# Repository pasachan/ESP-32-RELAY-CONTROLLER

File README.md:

# ESP32 Relay Controller

**An 8-channel relay controller with Wi-Fi, an RS-485 field bus, and a 12 V power rail for downstream nodes.**
Designed as the master board for a small home-automation network: this board switches loads directly, talks to
the outside world over Wi-Fi, and powers and polls a chain of low-cost slave boards (ATtiny / STM32 class) over RS-485.

Open hardware. KiCad 10 source, fabrication outputs, BOMs with LCSC part numbers, and a pick-and-place file are all in this repository. Rev 1 has been manufactured.

---

## Features

- **ESP32-WROOM-32D** (16 MB flash) — Wi-Fi + Bluetooth, USB-C programming via CH340C with auto-reset
- **8 × SPDT relays** (SRD-05VDC, 10 A contacts), driven by a ULN2803A with built-in flyback clamps, each brought out to a 3-way screw terminal (NO / COM / NC)
- **RS-485 half-duplex master** — MAX3485 (3.3 V), SM712 surge protection, jumper-selectable 120 Ω termination, fail-safe biasing
- **12 V field bus power** on the RS-485 connector, so slave nodes need no local supply
- **12 V input** with P-FET reverse-polarity protection, bidirectional TVS, and an LC input filter
- Two synchronous bucks (LMR51430): 5 V for relay coils, 3.3 V for logic — the 3.3 V rail also runs from USB alone for bench programming
- One dry-contact input (pull-up, RC filter, ESD clamp), active buzzer, WS2812B status LED, rail indicator LEDs
- RESET / BOOT / user (WPS) buttons, 2 mm mounting holes, 124.75 × 68 mm, 2-layer

---

## Block diagram

```mermaid
flowchart LR
    J1["12 V input"] --> Q1["IRF4905<br/>reverse-polarity FET"] --> L3["LC input filter"] --> V12["+12 V rail"]
    D2["SMBJ18CA TVS"] -.clamps.-> J1
    V12 --> U2["LMR51430<br/>buck → 5 V"] --> V5["+5 V coil rail"]
    V12 --> D3["Schottky OR"] --> U3["LMR51430<br/>buck → 3.3 V"] --> V33["+3.3 V logic"]
    USB["USB-C"] --> U4["USBLC6 ESD"] --> U6["CH340C"] <-->|"UART0 + auto-reset"| U1
    USB -->|"VBUS"| D4["Schottky OR"] --> U3
    V33 --> U1["ESP32-WROOM-32D"]
    U1 -->|"8 × GPIO"| U7["ULN2803A"] -->|"8 × coil"| K["K2 … K9<br/>SRD-05VDC SPDT"] --> JT["8 × NO/COM/NC<br/>screw terminals"]
    V5 --> K
    U1 <-->|"UART2 + DE/RE"| U9["MAX3485<br/>RS-485"] --> D6["SM712 TVS"] --> J12["Field bus<br/>12V · A · B · GND"]
    V12 --> J12
    U1 --> BZ["Buzzer"]
    U1 --> LED["WS2812B"]
    IN["Dry-contact input"] --> U1
```

---

## Specifications

| | |
|---|---|
| Supply | 12 V DC nominal (LMR51430 bucks accept 4–36 V; TVS clamps at 18 V standoff) |
| Board draw @ 12 V | ~170 mA idle · ~520 mA worst case (all relays + Wi-Fi TX) |
| Field-bus power budget | ~1.8 A at 12 V on J12 — set by the 1.0 mm feed trace (2.4 A @ 10 °C rise) less the board's own draw; L3 is rated 4.5 A |
| Relay contacts | SPDT, 10 A / 250 VAC rated · **PCB traces sized for ≤ 2.3 A at 12–30 V** (see [design notes](docs/design-notes.md#relay-bank-and-switched-load-clearances)) |
| Relay coil drive | ~4.0 V at the coil vs 3.75 V pick-up spec — all eight channels |
| RS-485 | Half-duplex, 3.3 V transceiver, 120 Ω termination via JP1, 330 Ω fail-safe bias (this node only) |
| USB | USB 2.0 Full Speed (CH340C), USB-C receptacle, 5.1 k CC pull-downs, VBUS ESD array |
| Logic level | 3.3 V throughout; WS2812B fed through a series diode so 3.3 V data meets its V<sub>IH</sub> |
| Dimensions | 124.75 × 68 mm, 1.6 mm FR-4, 2 layers, 1 oz copper |
| Mounting | 4 × Ø2.0 mm holes at the corners |

---

## Repository layout

```
esp32-relay-controller/
├── README.md
├── hardware/
│   ├── kicad/                     KiCad 10 project (schematic, PCB, custom rules, project symbol lib)
│   ├── fabrication/
│   │   ├── gerbers/               RS-274X gerbers + Excellon drill files (fab layers only)
│   │   ├── esp32-relay-controller-gerbers.zip
│   │   ├── BOM.csv                Master BOM — every fitted part, SMD and through-hole, with LCSC + MPN
│   │   ├── BOM-JLCPCB.csv         SMD-only, JLCPCB column format
│   │   ├── BOM-PCBWay.csv         SMD-only, MPN-first for PCBWay
│   │   ├── CPL.csv                SMD pick-and-place (Designator / Mid X / Mid Y / Layer / Rotation)
│   │   └── README.md              How to order
│   └── images/                    Renders and layer plots
├── docs/
│   ├── schematic.pdf
│   ├── design-notes.md            Design decisions, the review process, and what changed as a result
│   └── pinout.md                  ESP32 GPIO map, relay ↔ terminal ↔ GPIO table, connector pinouts
└── firmware/
    ├── README.md                  Pin definitions and the gotchas that bite firmware authors
    └── self-test/                 Bring-up sketch — exercises every component, no libraries needed
```

---

## Getting boards made

Everything a fab needs is in [`hardware/fabrication/`](hardware/fabrication/). The short version:

1. Upload `esp32-relay-controller-gerbers.zip` for the bare PCB — 2 layer, 1.6 mm, 1 oz, any colour.
2. For SMD assembly, upload `BOM-JLCPCB.csv` + `CPL.csv` (JLCPCB) or `BOM-PCBWay.csv` + `CPL.csv` (PCBWay). 72 SMD parts, 35 lines.
3. Hand-fit the 25 through-hole parts: 8 relays, 11 screw-terminal blocks, the TO-220 FET, buzzer, three tact switches and the termination header. All are common parts; LCSC numbers are in `BOM.csv`.

See [`hardware/fabrication/README.md`](hardware/fabrication/README.md) for gerber-origin caveats, the one DFM query a fab may raise, and which parts are safe to substitute.

---

## Firmware quick reference

[`firmware/self-test/`](firmware/self-test/) is a bring-up sketch that exercises every fitted component and prints a pass/fail report over USB serial. Run it first on a new board. Full map in [`docs/pinout.md`](docs/pinout.md), gotchas in [`firmware/README.md`](firmware/README.md).

| Function | GPIO | Notes |
|---|---|---|
| Relay 1 … 8 (silkscreen order) | 14, 19, 25, 13, 23, 33, 32, 18 | Active-high into ULN2803A |
| RS-485 TX / RX / DE+RE | 17 / 16 / 2 | GPIO2 has a 10 k pull-down → receive mode at boot |
| Dry-contact input | 34 | Input-only pin, external 10 k pull-up, closes to GND |
| User button (WPS) | 35 | Input-only, 10 k pull-down, pressed = high |
| Buzzer | 26 | Via NPN, active-high |
| WS2812B data | 27 | Through 330 Ω |
| UART0 (USB) | 1 / 3 | CH340C with DTR/RTS auto-reset |
| I²C | 21 / 22 | Routed to pads but **no pull-ups fitted** in rev 1 |

---

## Design notes

The interesting engineering is in [`docs/design-notes.md`](docs/design-notes.md). Highlights:

- **Why the field bus carries 12 V and not 3.3 V** — cable drop and the thermal ceiling of a SOT-23-6 buck make 3.3 V distribution a dead end past a couple of nodes; regulating at each slave costs one LDO and removes the constraint.
- **Reverse-polarity protection with a P-FET, and why the TVS sits in front of it** — a unidirectional clamp ahead of the FET would short a reversed supply, so it's a bidirectional part.
- **Relay coil drive margin** — the SRD-05VDC needs 3.75 V to pull in; behind a ULN2803A the coil sees ~4.0 V. A series diode in the original design put one channel *under* the limit and was removed.
- **Driving a 5 V WS2812B from a 3.3 V GPIO** — a diode in the LED's supply drops V<sub>DD</sub> into the window where 3.3 V is a valid high, without a level shifter.
- **A KiCad DRC gotcha** — custom rules that match on auto-generated net names like `Net-(J2-Pin_1)` silently never fire. The rules in this project match on a netclass instead.
- **What the design review caught** — the board went through a full netlist, DRC, ERC and geometric-connectivity audit before ordering; the findings and fixes are documented.

---

## Status

| Revision | Date | Notes |
|---|---|---|
| **Rev 1** | Sep 2026 | Ordered. 0 DRC errors, 0 unconnected nets, all nets verified single-island. |
| **Rev 1** | Oct 2026 | **Built and brought up.** All eight relays, the buzzer, the WS2812B, both inputs, the RS-485 receiver and the USB programming path work. One firmware-level finding: the MAX3485's RO pin is tri-stated during transmit and has no pull-up, so it needs one enabled in software — [details](firmware/self-test/README.md#finding-ro-floats-during-transmit). |

Known rev 1 limitations and the planned rev 2 changes are listed at the end of the [design notes](docs/design-notes.md#rev-2-backlog).

---

## Licence

Copyright © 2026 Pareekshit Sachan.

This source describes Open Hardware and is licensed under the **CERN-OHL-P v2** (`SPDX-License-Identifier: CERN-OHL-P-2.0`). You may redistribute and modify this documentation and make products using it under the terms of the CERN-OHL-P v2 — see [`LICENSE`](LICENSE) or <https://cern.ch/cern-ohl>.

This documentation is distributed WITHOUT ANY EXPRESS OR IMPLIED WARRANTY, INCLUDING OF MERCHANTABILITY, SATISFACTORY QUALITY AND FITNESS FOR A PARTICULAR PURPOSE. Please see the CERN-OHL-P v2 for applicable conditions.

Symbols, footprints and 3D models from the KiCad libraries are used under the [KiCad library licence](https://www.kicad.org/libraries/license/) (CC-BY-SA 4.0 with exception). Datasheets referenced in the design notes remain the property of their manufacturers.

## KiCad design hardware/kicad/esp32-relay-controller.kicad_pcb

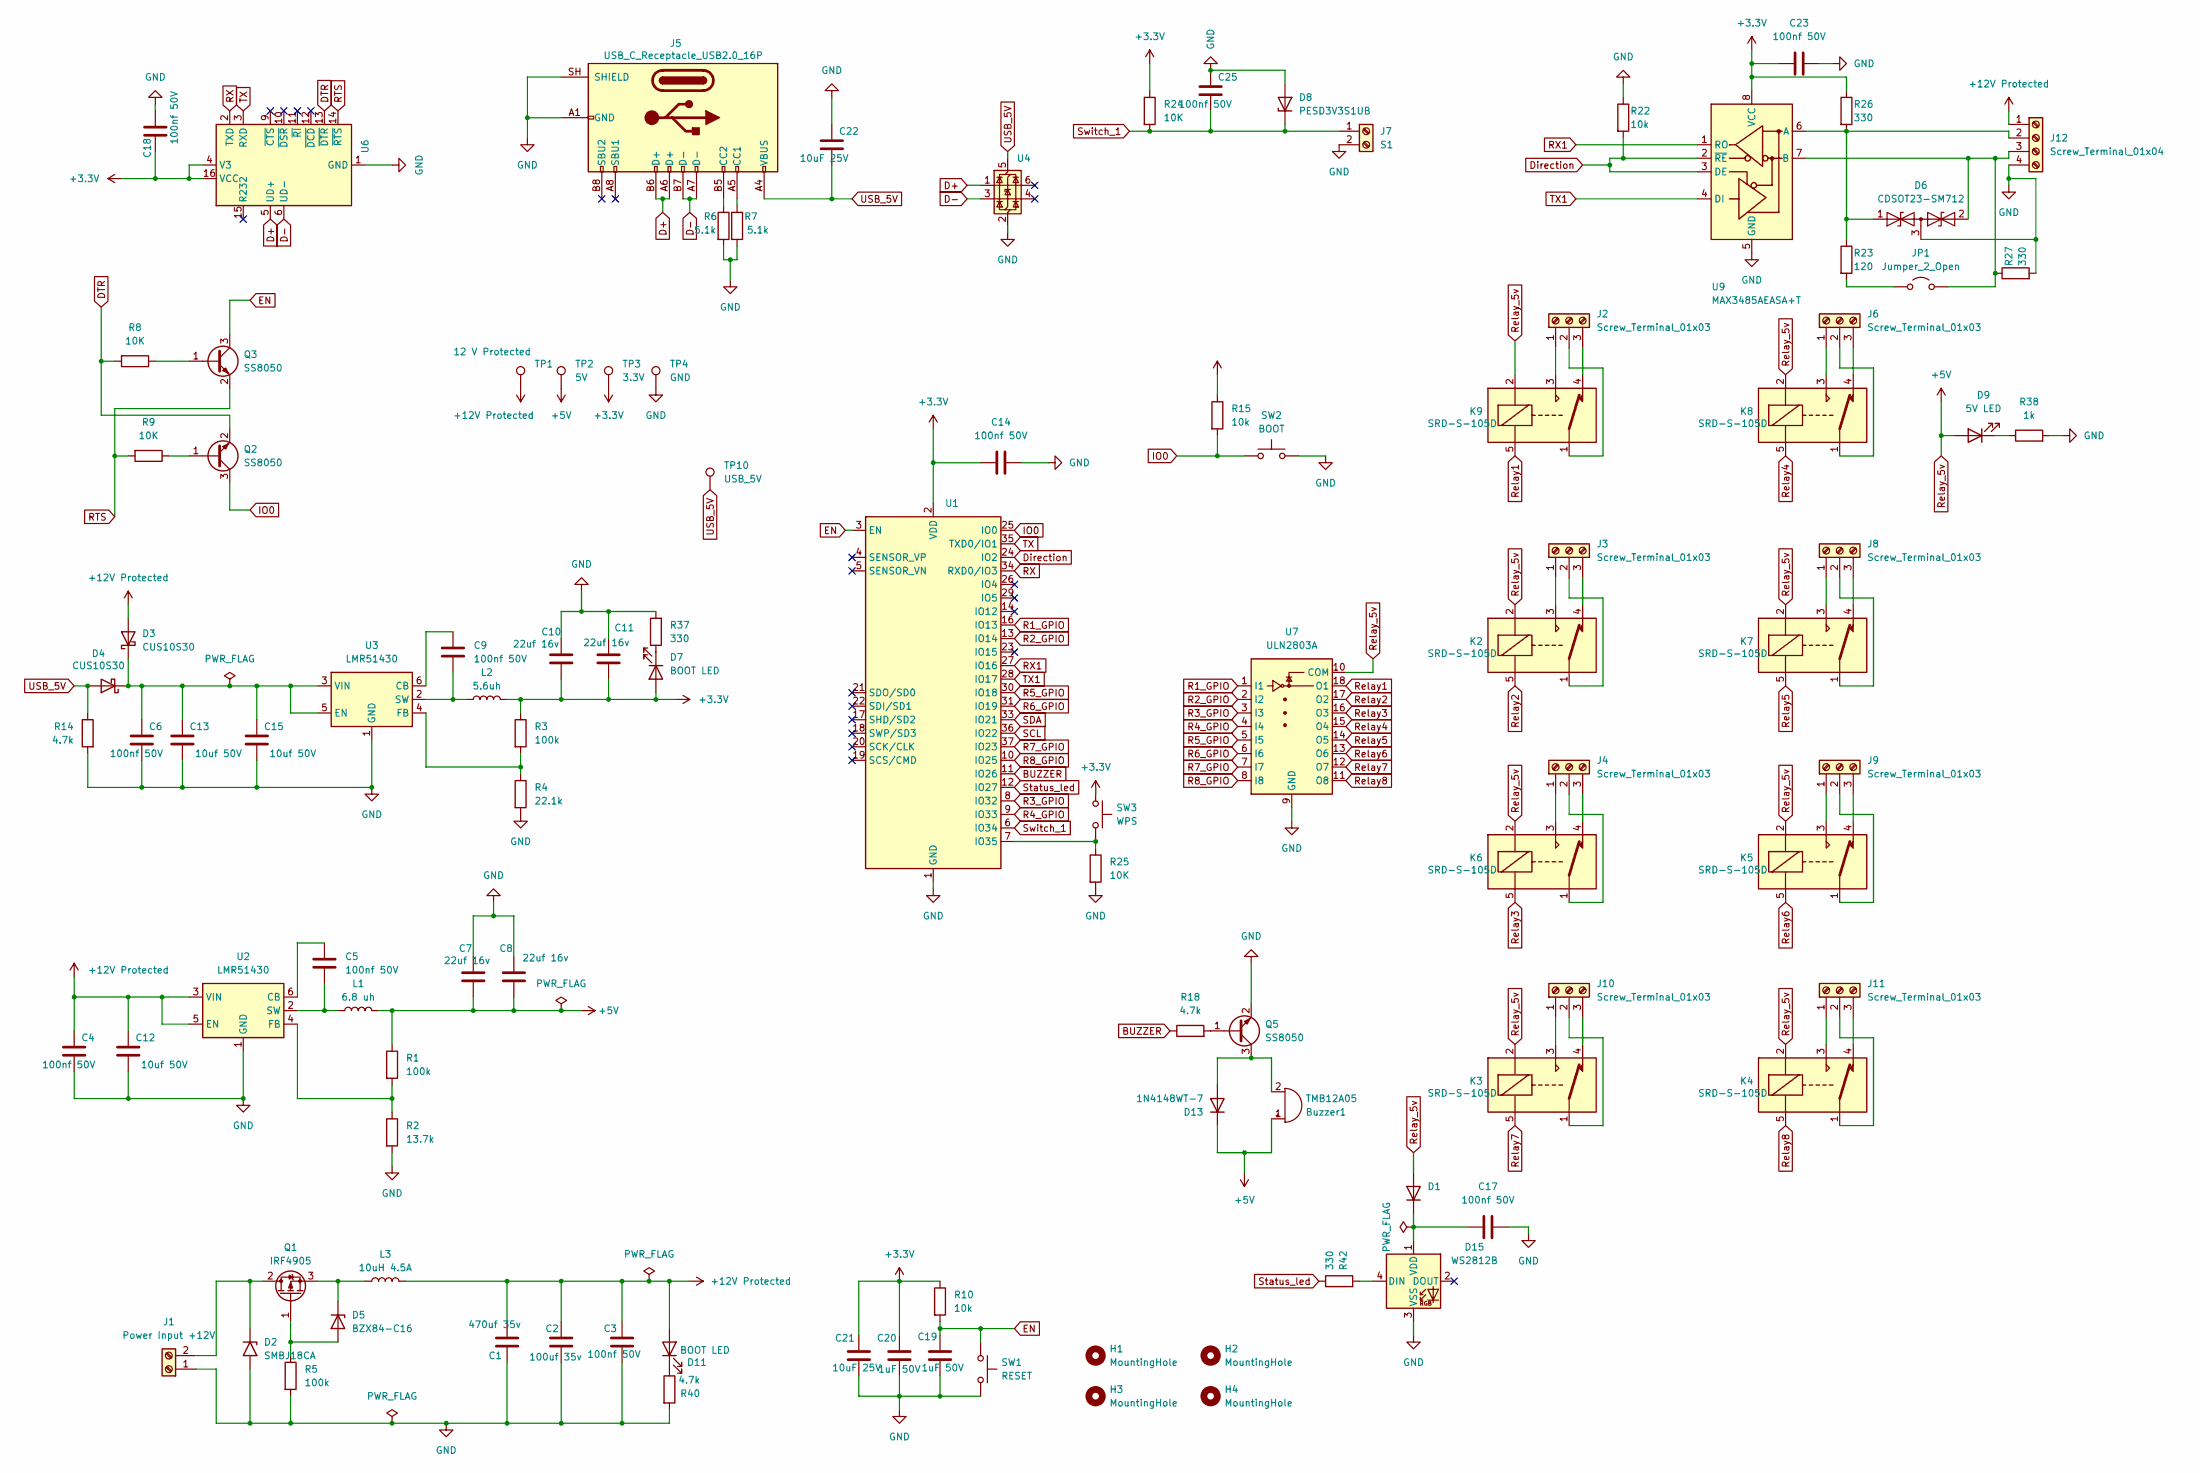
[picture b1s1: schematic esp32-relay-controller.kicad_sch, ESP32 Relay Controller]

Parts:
Buzzer1: TMB12A05; Buzzer_12x9.5RM7.6; MPN TMB12A05; LCSC C96093
C1: 470uf 35v; CP_Elec_10x10.5; MPN RVT1V471M1010 470UF 35V; LCSC C976030
C2: 100uf 35v; CP_Elec_6.3x7.7; MPN JBLM2101M035C070RTM 100UF 35V; LCSC C19270708
C3, C4, C5, C6, C9, C14, C17, C18, C23, C25: 100nf 50V; C_0603_1608Metric; MPN CL10B104KB8NNNC; LCSC C1591
C7, C8, C10, C11: 22uf 16v; C_0805_2012Metric; MPN CL21A226KOQNNNE; LCSC C296720
C12, C13, C15: 10uf 50V; C_0805_2012Metric; MPN GRM21BR61H106KE43L; LCSC C440198
C19, C20: 1uF 50V; C_0603_1608Metric; MPN CL10A105KB8NNNC; LCSC C15849
C21, C22: 10uF 25V; C_0603_1608Metric; MPN CL10A106MA8NRNC; LCSC C96446
D1, D13: 1N4148WT-7; D_SOD-523; MPN 1N4148WT-7; LCSC C83482
D2: SMBJ18CA; D_SMB; MPN SMBJ18CA; LCSC C2938922
D3, D4: CUS10S30; D_SOD-323; MPN CUS10S30; LCSC C27636107
D5: BZX84-C16; SOT-23; MPN BZX84-C16,235; LCSC C550938
D6: CDSOT23-SM712; SOT-23; MPN CDSOT23-SM712; LCSC C404012
D7, D11: BOOT LED; LED_0201_0603Metric; MPN CT-0201URC-P4; LCSC C52675906
D8: PESD3V3S1UB; D_SOD-523; MPN PESD3V3S1UB; LCSC C2912529
D9: 5V LED; LED_0201_0603Metric; MPN CT-0201URC-P4; LCSC C52675906
D15: WS2812B; LED_WS2812B_PLCC4_5.0x5.0mm_P3.2mm; MPN WS2812B-B/T; LCSC C2761795
H1, H2, H3, H4: MountingHole; MountingHole_2mm; MPN PCB feature
J1: Power Input +12V; TerminalBlock_MaiXu_MX126-5.0-02P_1x02_P5.00mm; MPN MX126-5.0-02P-GN01-Cu-S-A; LCSC C5188434
J2, J3, J4, J6, J8, J9, J10, J11: Screw_Terminal_01x03; TerminalBlock_MaiXu_MX126-5.0-03P_1x03_P5.00mm; MPN MX126-5.0-03P-GN01-Cu-S-A; LCSC C5188435
J5: USB_C_Receptacle_USB2.0_16P; USB_C_Receptacle_GCT_USB4105-xx-A_16P_TopMnt_Horizontal; MPN USB4105-GF-A-120; LCSC C5184243
J7: S1; TerminalBlock_MaiXu_MX126-5.0-02P_1x02_P5.00mm; MPN MX126-5.0-02P-GN01-Cu-S-A; LCSC C5188434
J12: Screw_Terminal_01x04; TerminalBlock_MaiXu_MX126-5.0-04P_1x04_P5.00mm; MPN MX126-5.0-04P-GN01-Cu-S-A
JP1: Jumper_2_Open; PinHeader_1x02_P2.54mm_Vertical; MPN PZ254V-11-02P; LCSC C492401
K2, K3, K4, K5, K6, K7, K8, K9: SRD-S-105D; Relay_SPDT_SANYOU_SRD_Series_Form_C; MPN SRD-S-105D; LCSC C276432
L1: 6.8 uh; L_Changjiang_FXL0630; MPN APH0630T6R8M; LCSC C5349706
L2: 5.6uh; L_Changjiang_FXL0630; MPN FXL0630-5R6-M; LCSC C475914
L3: 10uH 4.5A; L_Changjiang_FXL0630; MPN ZEMS0420-220M; LCSC C41438718
Q1: IRF4905; TO-220-3_Vertical; MPN IRF4905PBF; LCSC C2564
Q2, Q3, Q5: SS8050; SOT-23; MPN SS8050(RANGE:200-350); LCSC C2150
R1, R3, R5: 100k; R_0603_1608Metric; MPN 0603WAF1003T5E; LCSC C25803
R2: 13.7k; R_0603_1608Metric; MPN 0603WAF1372T5E; LCSC C22793
R4: 22.1k; R_0603_1608Metric; MPN FRC0603F2212TS; LCSC C2960862
R6, R7: 5.1k; R_0603_1608Metric; MPN 0603WAF5101T5E; LCSC C23186
R8, R9, R24, R25: 10K; R_0603_1608Metric; MPN 0603WAF1002T5E; LCSC C25804
R10, R15, R22: 10k; R_0603_1608Metric; MPN 0603WAF1002T5E; LCSC C25804
R14, R18, R40: 4.7k; R_0603_1608Metric; MPN 0603WAF4701T5E; LCSC C23162
R23: 120; R_0603_1608Metric; MPN 0603WAF1200T5E; LCSC C22787
R26, R27, R42: 330; R_0603_1608Metric; MPN 0603WAF3300T5E; LCSC C23138
R37: 330; R_0603_1608Metric; MPN 0603WAF1001T5E; LCSC C23138
R38: 1k; R_0603_1608Metric; MPN 0603WAF1001T5E; LCSC C21190
SW1: RESET; SW_PUSH_6mm; MPN TS-1102-4316; LCSC C111374
SW2: BOOT; SW_PUSH_6mm; MPN TS-1102-4316; LCSC C111374
SW3: WPS; SW_PUSH_6mm; MPN TS-1102-4316; LCSC C111374
TP1: 12 V Protected; TestPoint_Pad_D1.5mm; MPN PCB feature
TP2: 5V; TestPoint_Pad_D1.5mm; MPN PCB feature
TP3: 3.3V; TestPoint_Pad_D1.5mm; MPN PCB feature
TP4: GND; TestPoint_Loop_D2.50mm_Drill1.0mm; MPN Formed tinned wire loop
TP10: USB_5V; TestPoint_Pad_D1.5mm; MPN PCB feature
U1: ESP32-WROOM-32D; MPN ESP32-WROOM-32D-N16; LCSC C529578
U2, U3: LMR51430; SOT-23-6; MPN LMR51430XDDCR; LCSC C5185863
U4: USBLC6-2SC6; SOT-23-6; MPN USBLC6-2SC6; LCSC C7519
U6: CH340C; SOIC-16_3.9x9.9mm_P1.27mm; MPN CH340C; LCSC C84681
U7: ULN2803A; SOIC-18W_7.5x11.6mm_P1.27mm; MPN ULN2803A; LCSC C845537
U9: MAX3485AEASA+T; SOIC-8_3.9x4.9mm_P1.27mm; MPN MAX3485AEASA+T; LCSC C94609

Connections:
+3.3V: C10.2, C11.2, C14.1, C18.2, C20.1, C21.1, C23.1, D7.2 (A), L2.2, R3.1, R10.1, R15.1, R24.1, R26.1, SW3.1, TP3.1 (1_1), U1.2 (VDD), U6.4 (V3), U6.16 (VCC), U9.8 (VCC)
+12V Protected: C1.1, C2.1, C3.1, C4.1, C12.1, D3.2 (A), D11.2 (A), J12.1, L3.2, TP1.1 (1_1), U2.3 (VIN), U2.5 (EN)
BUZZER: R18.1, U1.11 (IO26)
D+: J5.A6 (D+), J5.B6 (D+), U4.1 (I/O1), U6.5 (UD+)
D-: J5.A7 (D-), J5.B7 (D-), U4.3 (I/O2), U6.6 (UD-)
DTR: Q2.2 (E), R8.2, U6.13 (~DTR)
Direction: R22.2, U1.24 (IO2), U9.2 (~RE), U9.3 (DE)
EN: C19.1, Q3.3 (C), R10.2, SW1.1, U1.3 (EN)
GND: C1.2, C2.2, C3.2, C4.2, C6.2, C7.1, C8.1, C10.1, C11.1, C12.2, C13.2, C14.2, C15.2, C17.2, C18.1, C19.2, C20.2, C21.2, C22.1, C23.2, C25.1, D2.2 (A2), D6.3 (common), D8.2 (A), D15.3 (VSS), J1.1, J5.A1 (GND), J5.A12 (GND), J5.B1 (GND), J5.B12 (GND), J5.SH (SHIELD), J7.2, J12.4, Q5.2 (E), R2.2, R4.2, R5.2, R6.2, R7.2, R14.2, R22.1, R25.2, R27.2, R37.2, R38.2, R40.2, SW1.2, SW2.2, TP4.1 (1_1), U1.1 (GND), U1.15 (GND), U1.38 (GND), U1.39 (GND), U2.1 (GND), U3.1 (GND), U4.2 (GND), U6.1 (GND), U7.9 (GND), U9.5 (GND)
IO0: Q2.3 (C), R15.2, SW2.1, U1.25 (IO0)
unnamed: Buzzer1.2 (-), D13.2 (A), Q5.3 (C)
unnamed: C17.1, D1.1 (K), D15.1 (VDD)
unnamed: D2.1 (A1), J1.2, Q1.2 (D)
unnamed: C6.1, C13.1, C15.1, D3.1 (K), D4.1 (K), U3.3 (VIN), U3.5 (EN)
unnamed: D5.1 (A), Q1.1 (G), R5.1
unnamed: D5.3 (K), L3.1, Q1.3 (S)
unnamed: D6.1 (A1), J12.2, R23.1, R26.2, U9.6 (A)
unnamed: D6.2 (A2), J12.3, JP1.2 (B), R27.1, U9.7 (B)
unnamed: D7.1 (K), R37.1
unnamed: D9.1 (K), R38.1
unnamed: D11.1 (K), R40.1
unnamed: D15.4 (DIN), R42.2
unnamed: J2.1, K9.3
unnamed: J2.2, K9.1
unnamed: J2.3, K9.4
unnamed: J3.1, K2.3
unnamed: J3.2, K2.1
unnamed: J3.3, K2.4
unnamed: J4.1, K6.3
unnamed: J4.2, K6.1
unnamed: J4.3, K6.4
unnamed: J5.A5 (CC1), R7.1
unnamed: J5.B5 (CC2), R6.1
unnamed: J6.1, K8.3
unnamed: J6.2, K8.1
unnamed: J6.3, K8.4
unnamed: J8.1, K7.3
unnamed: J8.2, K7.1
unnamed: J8.3, K7.4
unnamed: J9.1, K5.3
unnamed: J9.2, K5.1
unnamed: J9.3, K5.4
unnamed: J10.1, K3.3
unnamed: J10.2, K3.1
unnamed: J10.3, K3.4
unnamed: J11.1, K4.3
unnamed: J11.2, K4.1
unnamed: J11.3, K4.4
unnamed: JP1.1 (A), R23.2
unnamed: Q2.1 (B), R9.1
unnamed: Q3.1 (B), R8.1
unnamed: Q5.1 (B), R18.2
unnamed: R25.1, SW3.2, U1.7 (IO35)
unnamed: C5.1, U2.6 (CB)
unnamed: R1.2, R2.1, U2.4 (FB)
unnamed: C5.2, L1.1, U2.2 (SW)
unnamed: C9.1, U3.6 (CB)
unnamed: R3.2, R4.1, U3.4 (FB)
unnamed: C9.2, L2.1, U3.2 (SW)
R1_GPIO: U1.16 (IO13), U7.1 (I1)
R2_GPIO: U1.13 (IO14), U7.2 (I2)
R3_GPIO: U1.8 (IO32), U7.3 (I3)
R4_GPIO: U1.9 (IO33), U7.4 (I4)
R5_GPIO: U1.30 (IO18), U7.5 (I5)
R6_GPIO: U1.31 (IO19), U7.6 (I6)
R7_GPIO: U1.37 (IO23), U7.7 (I7)
R8_GPIO: U1.10 (IO25), U7.8 (I8)
RTS: Q3.2 (E), R9.2, U6.14 (~RTS)
RX: U1.34 (RXD0/IO3), U6.2 (TXD)
RX1: U1.27 (IO16), U9.1 (RO)
Relay1: K9.5, U7.18 (O1)
Relay2: K2.5, U7.17 (O2)
Relay3: K6.5, U7.16 (O3)
Relay4: K8.5, U7.15 (O4)
Relay5: K7.5, U7.14 (O5)
Relay6: K5.5, U7.13 (O6)
Relay7: K3.5, U7.12 (O7)
Relay8: K4.5, U7.11 (O8)
Relay_5v: Buzzer1.1 (+), C7.2, C8.2, D1.2 (A), D9.2 (A), D13.1 (K), K2.2, K3.2, K4.2, K5.2, K6.2, K7.2, K8.2, K9.2, L1.2, R1.1, TP2.1 (1_1), U7.10 (COM)
SCL: U1.36 (IO22)
SDA: U1.33 (IO21)
Status_led: R42.1, U1.12 (IO27)
Switch_1: C25.2, D8.1 (K), J7.1, R24.2, U1.6 (IO34)
TX: U1.35 (TXD0/IO1), U6.3 (RXD)
TX1: U1.28 (IO17), U9.4 (DI)
USB_5V: C22.2, D4.2 (A), J5.A4 (VBUS), J5.A9 (VBUS), J5.B4 (VBUS), J5.B9 (VBUS), R14.1, TP10.1 (1_1), U4.5 (VBUS)

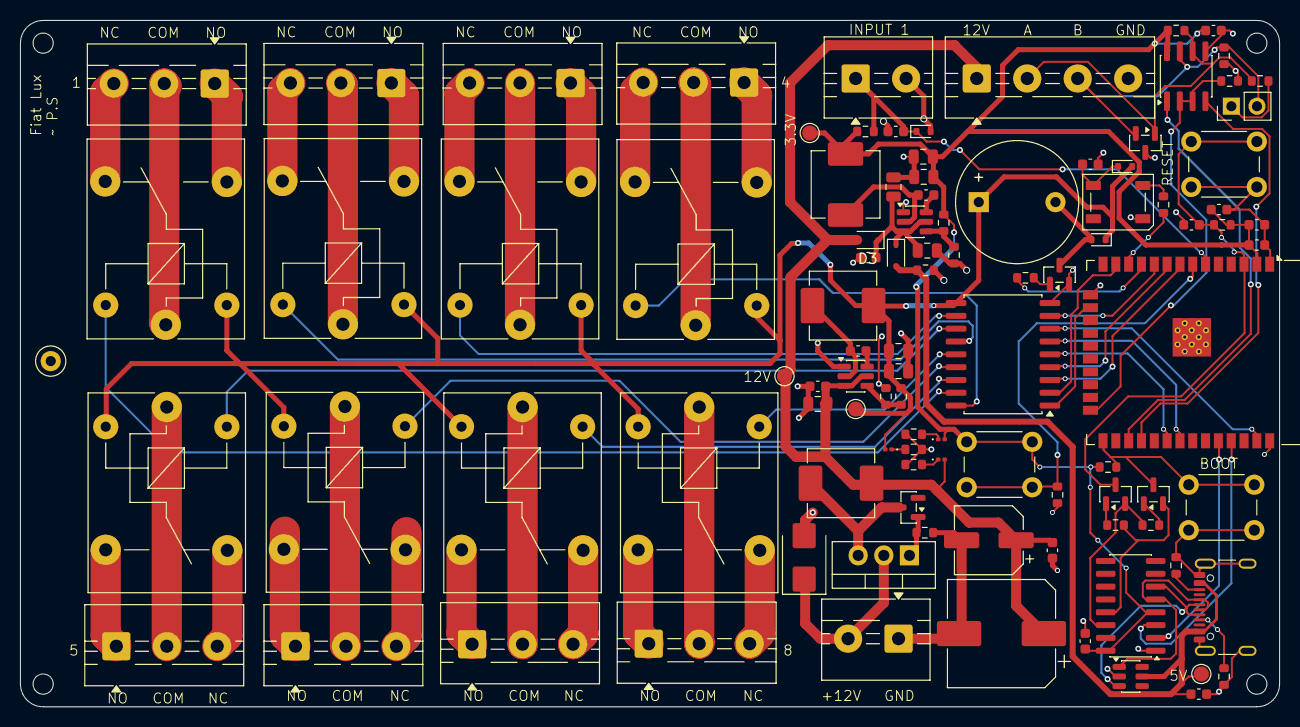
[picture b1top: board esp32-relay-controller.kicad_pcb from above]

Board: 2 copper layers, 124.8 x 68.0 mm, 106 parts (0 on the bottom side), 84 nets.

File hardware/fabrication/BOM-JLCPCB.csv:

Comment,Designator,Footprint,LCSC Part #
470uF 35V elec 105C,C1,CP_Elec_10x10.5,C976030
100uF 35V elec,C2,CP_Elec_6.3x7.7,C19270708
100nF 50V X7R,"C3,C4,C5,C6,C9,C14,C17,C18,C23,C25",C_0603_1608Metric,C1591
22uF 16V X5R,"C7,C8,C10,C11",C_0805_2012Metric,C296720
10uF 50V X5R,"C12,C13,C15",C_0805_2012Metric,C440198
1uF 50V X5R,"C19,C20",C_0603_1608Metric,C15849
10uF 25V X5R,"C21,C22",C_0603_1608Metric,C96446
1N4148WT-7 switching diode,"D1,D13",D_SOD-523,C83482
SMBJ18CA TVS 18V bidirectional,D2,D_SMB,C2938922
CUS10S30 Schottky 30V 1A,"D3,D4",D_SOD-323,C27636107
BZX84-C16 zener 16V,D5,SOT-23,C550938
CDSOT23-SM712 RS-485 TVS,D6,SOT-23,C404012
LED red 0201,"D7,D9,D11",LED_0201_0603Metric,C52675906
PESD3V3S1UB ESD 3.3V,D8,D_SOD-523,C2912529
WS2812B-B/T RGB LED,D15,LED_WS2812B_PLCC4_5.0x5.0mm_P3.2mm,C2761795
USB-C receptacle 16P,J5,USB_C_Receptacle_GCT_USB4105-xx-A_16P_TopMnt_Horizontal,C5184243
6.8uH inductor,L1,L_Changjiang_FXL0630,C5349706
5.6uH inductor,L2,L_Changjiang_FXL0630,C475914
10uH 4.5A molded inductor,L3,L_Changjiang_FXL0630,C167223
SS8050 NPN 1.5A,"Q2,Q3,Q5",SOT-23,C2150
100k 1%,"R1,R3,R5",R_0603_1608Metric,C25803
13.7k 1%,R2,R_0603_1608Metric,C22793
22.1k 1%,R4,R_0603_1608Metric,C2960862
5.1k 1%,"R6,R7",R_0603_1608Metric,C23186
10k 1%,"R8,R9,R10,R15,R22,R24,R25",R_0603_1608Metric,C25804
4.7k 1%,"R14,R18,R40",R_0603_1608Metric,C23162
120R 1%,R23,R_0603_1608Metric,C22787
330R 1%,"R26,R27,R37,R42",R_0603_1608Metric,C23138
1k 1%,R38,R_0603_1608Metric,C21190
ESP32-WROOM-32D-N16 module,U1,ESP32-WROOM-32D,C529578
LMR51430 buck 4-36V 3A,"U2,U3",SOT-23-6,C5185863
USBLC6-2SC6 USB ESD array,U4,SOT-23-6,C7519
CH340C USB-UART,U6,SOIC-16_3.9x9.9mm_P1.27mm,C84681
ULN2803A Darlington driver,U7,SOIC-18W_7.5x11.6mm_P1.27mm,C845537
MAX3485AEASA+T RS-485 transceiver,U9,SOIC-8_3.9x4.9mm_P1.27mm,C94609
